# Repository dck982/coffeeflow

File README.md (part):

# coffeeflow

Modification d'une **Profitec Go** pour du *flow profiling* et du *brew by weight* : l'infusion se lance depuis un écran tactile, la pression se module, et elle s'arrête toute seule au poids cible.

## Machine d'origine

- Vanne solénoïde trois voies + pompe vibratoire 35 W + boiler
- Petit boîtier PID : consigne / mesure de température du boiler, chrono
- Vanne OPV pour limiter la pression
- Plomberie en **1/8"**
- Connexions électriques internes : cosses à languette **FASTON 6,3 × 0,8 mm** (pas de piggyback : la dérivation se fait dans un boîtier imprimé)
- Deux compartiments : **technique** (hydraulique, boiler, groupe, électricité) et **réservoir d'eau**
- Bouton **brew** en façade (Ø 16 mm) : démarrait vanne + pompe. **Supprimé** — le trou sert de passe-câble CAN vers l'écran
- LED de façade : ses cosses FASTON ont été réutilisées, la LED est réalimentée depuis le boîtier PS

## Ce que la modification ajoute

La modification pilote la pompe, la vanne et la résistance de chaudière :

1. **Pompe** — un dimmer AC 4 A en mode **DimmerLink** (I2C) fait varier la pression.
2. **Vanne solénoïde** — un SSR ouvre et ferme le circuit d'infusion.
3. **Chaudière** — le SSR Keysolu/Maxwell fourni avec la machine commande la résistance de chauffe ; sa commande 5 V passe par un HW-399 dans `boitier_pid`.

Plus de bouton brew, plus de relais NC de « mode manuel » : la commande passe par l'écran. Le système est alimenté dès que l'**interrupteur principal** de la machine est enfoncé.

Deux retours capteurs, sur le module interne :

- **Pression** sur la plomberie, en amont de la vanne (I2C 3,3 V)
- **Débit** en amont de la pompe, côté basse pression (le capteur ne tient que 3 bar)

La **température de la chaudière** vient de la sonde NTC vissée en G1/8 dans la chaudière. Son câble rejoint le boîtier de l'écran, proche de la sonde, où un ADS1115 la mesure via un pont alimenté par le **3V3 et le GND du port Sensor AD du Waveshare**. Voir [la calibration NTC/ADS1115](docs/ntc_ads1115_calibration.md).

Le **poids** vient d'une balance **Acaia Lunar** en **BLE**, lue par l'écran. La pesée du drip tray par cellule de charge est **abandonnée pour l'instant** (peser quelques grammes sur un plateau d'un kilo) — pièces et cotes conservées dans `print/parts/*_pesage*` et `docs/driptray.md`.

## Architecture électronique

**Cinq boîtiers imprimés, deux nœuds ESP32-S3.** Le 230 V ne sort pas de la machine.

```
             interrupteur principal (230 V L/N)
                          │
                    [boitier_ps]      intérieur, face ouest, le long du réservoir
                  alim RECOM 5 W · Wago            │
                          │                        └── L/N → LED de façade
              ┌───────────┴───────────┐
          5 V / GND                 L/N ×2
              │                       │
   ┌──────────┴──────────┐      [boitier_ac]   accolé à boitier_dc
   │                     │       dimmer · SSR
[boitier_dc]        [screen_*]        │    │
 XIAO ESP32-S3       Waveshare 4,3"   │    └── L/N → vanne solénoïde
 + Grove Shield      ESP32-S3         └────── L/N → pompe vibratoire
 + CAN Pal           UI · Wi-Fi · BLE
      │                   └── I2C ← ADS1115 ← NTC chaudière
      │                   │
      └──── bus CAN ──────┘   paire torsadée, par le trou Ø16 de l'ex-bouton brew
      │
      ├── I2C 3,3 V ─→ dimmer (DimmerLink)
      ├── GPIO ──────→ SSR vanne (M5Stack Unit SSR)
      ├── GPIO 3 ────→ [boitier_pid : HW-399] ─→ SSR chaudière ─→ résistance
      ├── I2C 3,3 V ←─ capteur de pression XDB401
      └── GPIO ──────← débitmètre Digmesa
```

| Nœud | Alias | Où | Rôle |
| --- | --- | --- | --- |
| **Waveshare 4,3" LCD Touch** (ESP32-S3-WROOM) | *screen*, *écran*, *waveshare* | façade, dans `screen_base` + `screen_wedge` | Interface utilisateur, algorithme d'infusion, **Wi-Fi et BLE** (Acaia Lunar) ; raccordement de la NTC chaudière via ADS1115 |
| **Seeed XIAO ESP32-S3** sur Grove Shield | *xiao*, *module interne*, *module capteurs*, *contrôleur* | intérieur, `boitier_dc`, zone froide entre le module PID et le cadran manomètre | Capteurs (XDB401, Digmesa) et actionneurs (dimmer pompe, SSR vanne, commande du SSR chaudière via HW-399) |

Les deux nœuds parlent **CAN**. L'écran est le seul à utiliser la radio.

Maquette Three.js de la machine (ouvrir dans le navigateur) : `docs/profitec_go.html`.

### Pourquoi un XIAO à l'intérieur

L'Atom Echo S3R de l'ancienne architecture est spécifié à **40 °C**. Le XIAO ESP32-S3 tient **85 °C**. Le compartiment technique monte à 45–50 °C : la marge de l'Atom est nulle, celle du XIAO est utilisable. L'écran Waveshare reste en façade, hors de cette enceinte.

---

## Boîtiers

| Boîtier | Pièces `print/parts/` | Où | Contenu |
| --- | --- | --- | --- |
| **PS** | `boitier_ps`, `couvercle_ps` | intérieur, contre la face **gauche** vue de face, le long de la séparation avec le réservoir | Alim RECOM, Wago 230 V (entrée + LED façade), Wago 5 V / GND |
| **DC** | `boitier_dc` | intérieur, **zone froide** entre le module PID et le cadran manomètre | XIAO + Grove Shield, Adafruit CAN Pal, Wago 5 V |
| **AC** | `boitier_ac` | accolé au DC | Dimmer 4 A DimmerLink, M5Stack Unit SSR |
| **PID** | `boitier_pid`, `couvercle_pid` | compartiment technique, près du contrôleur PID d'origine | HW-399, connecteurs XH et Wago de distribution 5 V / GND ; commande du SSR chaudière |
| **UI** | `screen_base`, `screen_wedge` | façade de la machine | Écran Waveshare 4,3", ADS1115 et raccordement NTC ; emplacement AMS1117 inutilisé |

Les boîtiers **AC et DC sont côte à côte et reliés par leur couvercle**, qui est commun aux deux (`couvercle_acdc`, assemblage `ensemble_boitiers`).

---

## Composants

| Rôle | Matériel retenu | Fiche |
| --- | --- | --- |
| UI / algo / radio | **Waveshare ESP32-S3-Touch-LCD-4.3** — 800 × 480, TJA1051T/3 CAN intégré, alim USB-C 5 V | `docs/datasheets/waveshare-4-3-lcd-touch.md` |
| MCU interne | **Seeed Studio XIAO ESP32-S3** sur **Grove Shield for XIAO** (8 ports Grove) | `docs/datasheets/xiao.pdf`, `docs/datasheets/grove-expansion-board.md` |
| Transceiver CAN côté XIAO | **Adafruit CAN Pal** (TJA1051T/3), [produit 5708](https://www.adafruit.com/product/5708) | — |
| Dimmer pompe | **RBDimmer AC Dimmer 4 A 1 canal**, logique 3,3 V, mode **[DimmerLink](https://www.rbdimmer.com/docs/dimmerlink-overview)** ([boutique](https://www.rbdimmer.com/shop/ac-dimmers-1/ac-dimmer-module-4a-1-channel-33v5v-logic-ac-400v-4a-6?attribute_values=48)) | — |
| SSR vanne | **M5Stack Unit SSR** (2 A), commande 3,3–5 V, zero-crossing MOC3043M | `docs/datasheets/m5stack-unit-ssr.md` |
| SSR chaudière | **Keysolu/Maxwell KS53 D-24Z20N-LQ**, fourni avec la machine ; en série entre la phase de l'interrupteur principal et la résistance, suivie de la protection thermique puis du neutre ; commande DC +/− via HW-399, FASTON mâles 4,8 mm | [Câblage](docs/cablage.md#ssr-de-chaudière-fourni-avec-la-machine) |
| Interface SSR chaudière | **HW-399 4-channel Optocoupler**, voie IN4 / OUT4, logé dans `boitier_pid` | `docs/cablage.md` |
| Température chaudière | Sonde **NTC G1/8**, pont sur le port Sensor AD et breakout **ADS1115 16 bits** sur l'I2C de l'écran | [Calibration NTC/ADS1115](docs/ntc_ads1115_calibration.md) |
| Pression | **Yufavor XDB401**, I2C, filetage **G1/8** | `docs/datasheets/xidibei_xdb401.pdf` |
| Débit | **Digmesa FHKSC 932-9525-B**, buse **1,00 mm** | `docs/datasheets/flowmeter-digmesa.pdf`, `docs/debitmetres.md` |
| Alimentation | **RECOM RAC05-05SK/277/W** — 5 W, 5 V / 1 A, encapsulée, 85–305 VAC, version fils | `docs/datasheets/RAC05-K_277.pdf` |
| Poids | **Acaia Lunar**, BLE, lue par l'écran | — |
| Câble | **Helutherm 145** — 0,75 mm² pour les ajouts 230 V, 0,25 mm² en 5 V / signaux / CAN ; puissance chaudière en 1 mm² | `docs/datasheets/helutherm145.pdf` |

Actionneurs d'origine pilotés : vanne solénoïde **OLAB 08252L50-A14-1A-G** (bobine 08000BH-J5IV, 15 VA, 220/230 V 50/60 Hz, orifice Ø 1,4 mm, joint FKM, laiton CW510L, NSF) et pompe vibratoire **OLAB Silent Green 35 W**.

---

## Le module interne (XIAO)

### Ports Grove du Shield

Le Shield expose **deux colonnes de quatre connecteurs**. XIAO en bas : colonne de **gauche = L**, colonne de **droite = R** ; le port le plus proche du XIAO est **1**, le plus éloigné **4**.

| Port | Périphérique | Bus / GPIO | Alim | Câble |
| --- | --- | --- | --- | --- |
| **R1** | Capteur de pression XDB401 | I2C — SDA **GPIO 5**, SCL **GPIO 6** | 3,3 V | Grove à clip (quelques cm) → JST SM 4 pôles, débrochable **hors du boîtier** |
| **R2** | Débitmètre Digmesa | impulsions — **GPIO 44** (D7 sur le PCB) | 5 V (voir ci-dessous) | Grove 2 fils (noir + jaune) → JST SM 3 pôles → VH3.96 côté Digmesa |
| **R3** | Adafruit CAN Pal | TWAI — TX **GPIO 7** (fil blanc), RX **GPIO 8** (fil jaune) | 3,3 V | Grove → fils dénudés dans le bornier à vis du CAN Pal |
| **R4** | M5Stack Unit SSR, **vanne** | commande — **GPIO 9** (D10, fil jaune) | 5 V, repris hors du câble | Grove 10 cm, VCC coupé à ras côté XIAO |
| **L2** | HW-399 → SSR **chaudière** | commande — **GPIO 3** (D2 sur le PCB), LOW = chauffe active | 5 V côté sortie du HW-399 | Grove → XH 2 pôles (GND, IN4) ; XH 3 pôles (GND, VCC, OUT4) côté sortie |
| **L4** | Dimmer DimmerLink | I2C — SDA **GPIO 5**, SCL **GPIO 6** | 3,3 V | Grove |

Les repères `Dn` imprimés sur le Shield ne correspondent pas toujours aux GPIO natifs du XIAO. Le [tableau de câblage](docs/cablage.md#ports-grove-du-xiao) donne les deux numérotations.

**L4 est câblé en copie de R1** pour exposer une deuxième prise I2C. Le dimmer et le capteur de pression sont donc **sur le même bus** : le dimmer n'a pas de pull-up, il profite des **4,7 kΩ du XDB401**. Conséquence : retirer le capteur de pression laisse SDA / SCL sans tirage et le dimmer ne répond plus (sauf câble très court, sur les pull-ups internes de l'ESP32). Ne pas empiler un second 4,7 kΩ côté MCU tant que le XDB401 est sur le bus.

### Pastilles du Shield

Le Shield porte une rangée de pastilles à **gauche du XIAO** (carte tenue XIAO en bas, ports vers le haut). Les trois premières sont **5 V**, **GND**, **3V3** ; la septième est **D7 / GPIO 44**.

- Un **bornier 2 poles** est soudé sur les pastilles 5 V et GND : il alimente le XIAO depuis le boîtier PS et sert de point de reprise.
- **Filtre RC du débitmètre** : résistance **1 kΩ** entre la pastille 3 (3V3) et la pastille D7 (GPIO 44), condensateur **10 nF** à cheval entre la pastille 2 (GND) et la pastille D7. Le Digmesa est un collecteur ouvert NPN : il tire la ligne à la masse mais ne la monte jamais, c'est le tirage vers 3,3 V qui fixe le niveau haut, alors même que le capteur est alimenté en 5 V. GPIO en `INPUT`, pull-up interne éteinte.

### Bus CAN

Le CAN Pal est monté au **nord de `boitier_dc`**.

- Un **bornier à vis 2,54 mm** est soudé sur ses **quatre pastilles de gauche** (VCC, GND, RX, TX de gauche à droite) et rejoint le port **R3** par un câble dénudé d'un côté, Grove de l'autre.
- Les **deux pastilles de droite** (CANH, CANL) portent un **connecteur PCB femelle JST XH 2,54 mm**.
- La ligne est une **paire torsadée Helutherm 145 0,25 mm²** : **CANL = orange, CANH = gris**. Elle chemine dans la machine et sort par le trou de l'ancien bouton brew, équipé du passe-câble imprimé (`passe_cable` + `ecrou_passe_cable`).
- À l'autre bout, un **JST SM 2 poles** la relie à un câble **JST PH 2.0 2 poles** qui se branche sur le PCB du Waveshare (transceiver TJA1051T/3 intégré, CAN sur **GPIO15 TX / GPIO16 RX**, `CAN_SEL` = EXIO5 à l'état haut).
- Les **résistances de terminaison 120 Ω sont activées par jumper des deux côtés**.

---

## Alimentation

L'alim **RECOM RAC05-05SK/277/W** vit dans `boitier_ps` et alimente **tout** : les deux modules, les capteurs et les actionneurs basse tension.

### 230 V

- **Phase et neutre** viennent de deux **cosses FASTON isolées** prises sur l'**interrupteur principal** de la machine : tant qu'il n'est pas enfoncé (clic mécanique), rien n'est sous tension.
- Les deux fils (**Helutherm 145 0,75 mm²**) entrent dans `boitier_ps` par le **sud-ouest** et vont dans les deux Wago (**phase en bas, neutre en haut**).
- De ces mêmes Wago, phase et neutre **ressortent par le sud-ouest** pour alimenter la **LED de façade** — nécessaire, ses cosses FASTON ayant été réutilisées. **Phase brun, neutre bleu.**
- Phase et neutre ressortent aussi en **arc vers le nord** pour alimenter la RECOM, juste au nord dans le même boîtier. **Phase brun, neutre bleu.**
- Deux paires 0,75 mm² sortent vers `boitier_ac`, entrant par sa **face est**, chaque paire phase-neutre maintenue par de la gaine thermo (surface de boucle nulle) : **SSR (jaune/bleu)** et **dimmer (violet/bleu)**.
- Du **SSR** repartent phase et neutre vers la **vanne solénoïde** — **phase jaune, neutre bleu**.
- Du **dimmer** repartent phase et neutre vers la **pompe** — **phase violet, neutre bleu**.

### 5 V

- **VCC 5 V et GND** sortent de la RECOM vers les **Wago 3 poles au nord de `boitier_ps`**.
- De là, deux fils **0,25 mm² rouge / noir** vont à l'**écran**, via un **bornier adaptateur USB-C**.
- Deux autres fils rouge / noir vont à `boitier_dc`, dans les deux Wago du **compartiment sud-ouest** : **3 poles à gauche = 5 V**, **2 poles à droite = GND**.
- De ces bornes partent (a) le 5 V / GND du **XIAO**, par le bornier soudé aux pastilles du Shield, et (b) le 5 V vers la **Wago 3 poles du compartiment nord-ouest**.
- La Wago nord-ouest distribue le 5 V au **SSR** (fil du câble Grove dont le VCC a été coupé à ras côté XIAO, dénudé et repris ici) et au **Digmesa** (fil rouge du câble JST SM).
- Le `boitier_pid` reçoit aussi le **5 V / GND** pour les Wago et la sortie du HW-399 qui commande le SSR chaudière. Le pont NTC du boîtier de l'écran utilise le **3V3 / GND du port Sensor AD du Waveshare**.

### Le câble du Digmesa

Côté JST SM : **3 poles, 3 fils — rouge, noir, jaune**.

- **noir + jaune** sont sertis dans un connecteur **Grove** → port **R2**
- **rouge** part seul dans la **Wago du compartiment nord-ouest** → 5 V

Côté capteur, le câble est en **VH3.96** : rouge = VCC, noir = GND, jaune = signal.

---

## Capteurs

### Température chaudière — NTC G1/8

La sonde rejoint directement le boîtier de l'écran, voisin de la chaudière. Le **3V3 du port Sensor AD du Waveshare** rejoint la Wago NTC2, la NTC et l'entrée **A0** de l'ADS1115 ; le retour NTC rejoint la Wago NTC1, **A1** et une résistance mesurée de **2,193 kΩ** vers le **GND du même port Sensor AD**. L'ADS1115 16 bits est sur le port I2C du Waveshare. A0 permet de mesurer la tension réelle d'alimentation du pont. Le LDO AMS1117 du montage initial a été retiré après la correction de la référence de masse. Schéma et paramètres de conversion : [calibration NTC/ADS1115](docs/ntc_ads1115_calibration.md).

### Pression — Yufavor XDB401

Quatre fils : **rouge VCC**, **noir GND**, **vert SDA**, **blanc SCL**. Alimenté en **3,3 V** (l'emballage annonce 5 V ; l'émulation XDB401 est complète en 3,3 V, vérifié au banc). Pull-up **4,7 kΩ** sur SDA et SCL, non débrayables — ce sont elles qui tiennent tout le bus. Filetage **G1/8**, d'où le choix (plomberie machine en 1/8").

Gaine silicone avec une **fine feuille de blindage** : **pas de continuité feuille ↔ GND**. La relier à la masse **uniquement côté ESP32** ; côté sonde, coupée et isolée, pas de boucle.

Le connecteur **JST SM** est à l'extérieur du boîtier, à proximité immédiate : la sonde se débranche sans ouvrir.

### Débit — Digmesa FHKSC 932-9525-B (buse 1,00 mm)

| | 932-9525-B (retenu) | 932-9521-A (ancien) |
| --- | --- | --- |
| Buse | **1,00 mm** | 1,20 mm |
| Sens de montage | 0° | 0° |
| Impulsions | **2382 imp/L (0,42 g)** | 1925 imp/L (0,519 g) |
| Plage linéaire | **0,033 – 0,40 L/min** | 0,075 – 0,569 L/min |
| Pré-infusion 0,5 g/s | bas de plage | sous le linéaire |
| Perte de charge | ~0,48 bar vers 0,40 L/min | ~0,42 bar à 0,6 L/min |
| **Pression max** | **3 bar à 20 °C** | 3 bar à 20 °C |

Deux conséquences qui ne relèvent pas du câblage :

- **Le capteur va en amont de la pompe**, entre le réservoir et son entrée. La machine infuse à 9 bar et la pompe monte plus haut avant l'OPV : 3 bar de tenue interdisent le circuit haute pression.
- Le **1,00 mm** met une extraction de 36 g / 28 s (0,077 L/min) à 2,3 × son minimum, et 0,5 g/s au début du linéaire. Plafond 0,40 L/min : une chasse pompe ouverte peut saturer. Comparatif complet : `docs/debitmetres.md`.

---

## Câblage

| Domaine | Fil | Connectique |
| --- | --- | --- |
| 230 V — ajouts pompe/vanne/alimentation | **Helutherm 145 0,75 mm²**, paires L/N sous gaine thermo | Wago 221 à leviers ; FASTON 6,3 × 0,8 mm côté machine |
| 230 V — puissance chaudière | **1 mm²** | SSR chaudière fourni avec la machine, FASTON mâles 4,8 mm |
| 5 V / signaux / CAN | **Helutherm 145 0,25 mm²** | Grove, JST SM (débrochable), JST XH / PH 2.0, borniers à vis 2,54 mm, Wago 221 |

Détail fil par fil, couleurs et cheminement : `docs/cablage.md`. Passage intérieur → façade : le trou **Ø 16 mm** de l'ancien bouton brew, avec le passe-câble imprimé.

## Firmware

- **`boitier_dc` (XIAO ESP32-S3)** — I2C (DimmerLink, XDB401), GPIO du SSR vanne et du SSR chaudière, comptage d'impulsions du débitmètre, TWAI/CAN.
- **UI (Waveshare ESP32-S3)** — affichage et commandes, **algorithme d'infusion** (flow control, stop on weight), Wi-Fi, BLE vers l'Acaia Lunar. L'ADS1115 sur son I2C mesure la température chaudière par une NTC.

**Langage : Rust** (`no_std`, esp-hal, embassy) sur les deux cartes, sous `firmware/rust/` ; l'interface de l'écran est en **Slint**. Le firmware C++/ESP-IDF d'origine est archivé dans `archive/firmware/`, toujours compilable : il reste la référence de comportement sur le bus CAN et en HTTP. L'outil Mac `coffeetool` (Rust) remplace les scripts Python, archivés eux aussi.

**État du firmware (2026-10-09) :** écran et module capteurs en **0.4.2**, installés et validés sur la machine, démarrage à froid compris : affichage, BLE et Wi-Fi ensemble, CAN, mise à jour de l'écran par HTTP et du module capteurs par le CAN, retour en arrière automatique. Restent à valider sur la machine : chauffe, purge et infusion. Voir [le contrat firmware](docs/firmware.md) et [la calibration NTC](docs/ntc_ads1115_calibration.md).

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
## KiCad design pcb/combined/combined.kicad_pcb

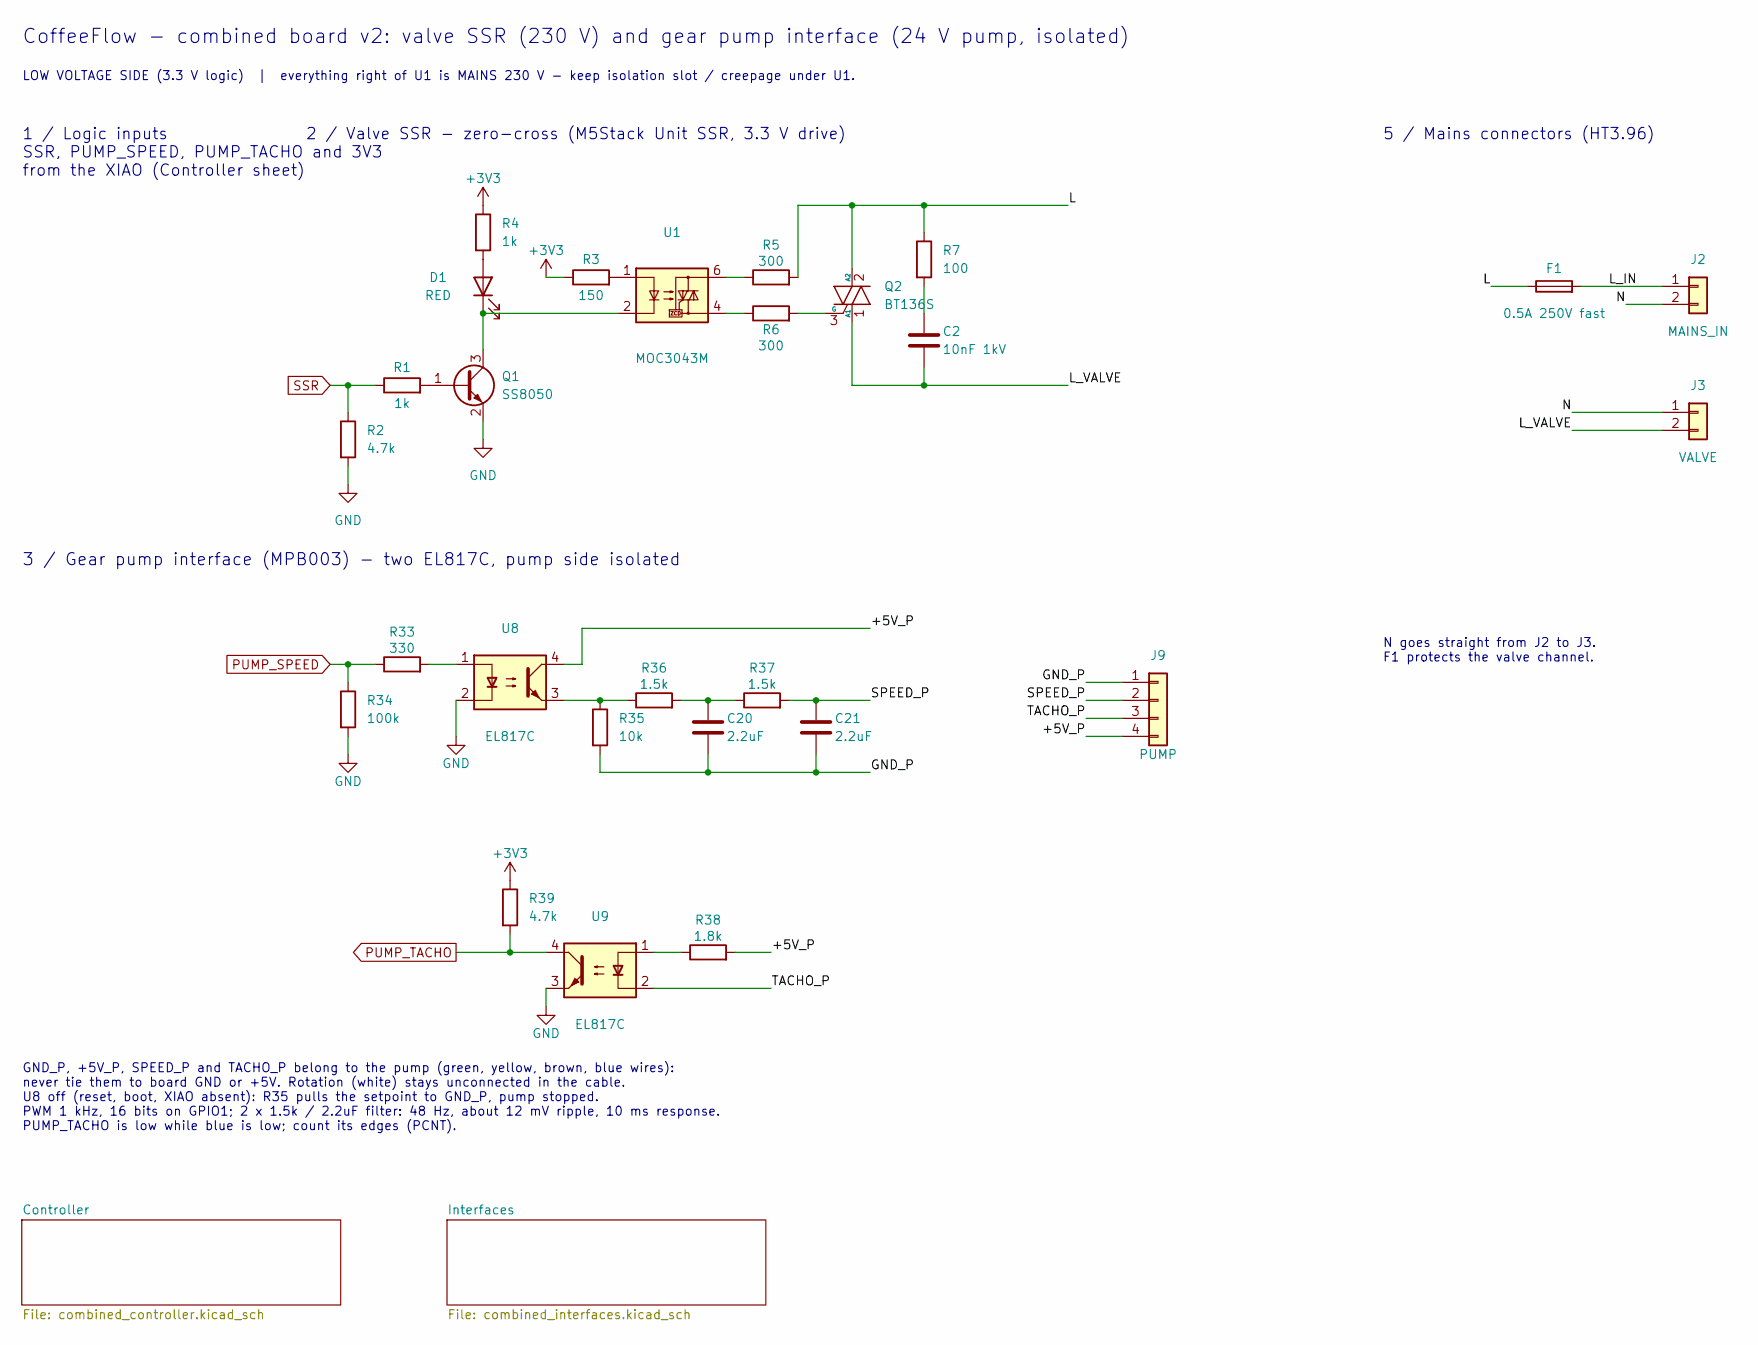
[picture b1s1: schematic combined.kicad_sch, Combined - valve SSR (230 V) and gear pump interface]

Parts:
C2: 10nF 1kV; C_1812_4532Metric; MPN FV43X103K102EFG; LCSC C394164
C20, C21: 2.2uF; C_0805_2012Metric; MPN CL21A225KBQNNNE; LCSC C377773
D1: RED; LED_0603_1608Metric; MPN KT-0603R; LCSC C2286
F1: 0.5A 250V fast; F2410; MPN MF2410F0.500TM; LCSC C91409
J2: MAINS_IN; CONN-TH_P3.96_HT396R-3.96-2P; MPN MXHT396R-3.96-02P-OE01-Cu-A; LCSC C48688287
J3: VALVE; CONN-TH_P3.96_HT396R-3.96-2P; MPN MXHT396R-3.96-02P-OE01-Cu-A; LCSC C48688287
J9: PUMP; JST_XH_B4B-XH-A_1x04_P2.50mm_Vertical; MPN B4B-XH-A(LF)(SN); LCSC C144395
Q1: SS8050; SOT-23; MPN SS8050 (Y1); LCSC C2150
Q2: BT136S; TO-252-2; MPN BT136S; LCSC C23427
R1, R4: 1k; R_0603_1608Metric; MPN 0603WAF1001T5E; LCSC C21190
R2, R39: 4.7k; R_0603_1608Metric; MPN 0603WAF4701T5E; LCSC C23162
R3: 150; R_0603_1608Metric; MPN 0603WAF1500T5E; LCSC C22808
R5, R6: 300; R_1206_3216Metric; MPN 1206W4F3000T5E; LCSC C17887
R7: 100; R_1206_3216Metric; MPN 1206W4F1000T5E; LCSC C17901
R33: 330; R_0603_1608Metric; MPN 0603WAF3300T5E; LCSC C23138
R34: 100k; R_0603_1608Metric; MPN 0603WAF1003T5E; LCSC C25803
R35: 10k; R_0603_1608Metric; MPN 0603WAF1002T5E; LCSC C25804
R36, R37: 1.5k; R_0603_1608Metric; MPN 0603WAF1501T5E; LCSC C22843
R38: 1.8k; R_0603_1608Metric; MPN 0603WAF1801T5E; LCSC C4177
U1: MOC3043M; SMDIP-6_W9.53mm_Slot; MPN MOC3043SR2M; LCSC C41809
U8, U9: EL817C; SMDIP-4_W9.53mm; MPN EL817S1(C)(TU)-F; LCSC C2912100

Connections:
+3V3: R3.1, R4.1, R39.1; also elsewhere on the board
/+5V_P: J9.4, R38.2, U8.4
/GND_P: C20.2, C21.2, J9.1, R35.2
/L: F1.1, Q2.2 (A2), R5.2, R7.1
/L_IN: F1.2, J2.1
/L_VALVE: C2.2, J3.2, Q2.1 (A1)
/N: J2.2, J3.1
/SPEED_P: C21.1, J9.2, R37.2
/TACHO_P: J9.3, U9.2
GND: Q1.2 (E), R2.2, R34.2, U8.2, U9.3; also elsewhere on the board
unnamed: C2.1, R7.2
unnamed: C20.1, R36.2, R37.1
unnamed: D1.2 (A), R4.2
unnamed: D1.1 (K), Q1.3 (C), U1.2
unnamed: Q1.1 (B), R1.2
unnamed: Q2.3 (G), R6.2
unnamed: R3.2, U1.1
unnamed: R5.1, U1.6
unnamed: R6.1, U1.4
unnamed: R33.2, U8.1
unnamed: R35.1, R36.1, U8.3
unnamed: R38.1, U9.1
PUMP_SPEED: R33.1, R34.1; also elsewhere on the board
PUMP_TACHO: R39.2, U9.4; also elsewhere on the board
SSR: R1.1, R2.1; also elsewhere on the board

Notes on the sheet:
2 / Valve SSR - zero-cross (M5Stack Unit SSR, 3.3 V drive)
5 / Mains connectors (HT3.96)
1 / Logic inputs SSR, PUMP_SPEED, PUMP_TACHO and 3V3 from the XIAO (Controller sheet)
N goes straight from J2 to J3. F1 protects the valve channel.
CoffeeFlow - combined board v2: valve SSR (230 V) and gear pump interface (24 V pump, isolated)
LOW VOLTAGE SIDE (3.3 V logic) | everything right of U1 is MAINS 230 V - keep isolation slot / creepage under U1.
3 / Gear pump interface (MPB003) - two EL817C, pump side isolated
GND_P, +5V_P, SPEED_P and TACHO_P belong to the pump (green, yellow, brown, blue wires): never tie them to board GND or +5V. Rotation (white) stays unconnected in the cable. U8 off (reset, boot, XIAO absent): R35 pulls the setpoint to GND_P, pump stopped. PWM 1 kHz, 16 bits on GPIO1; 2 x 1.5k / 2.2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

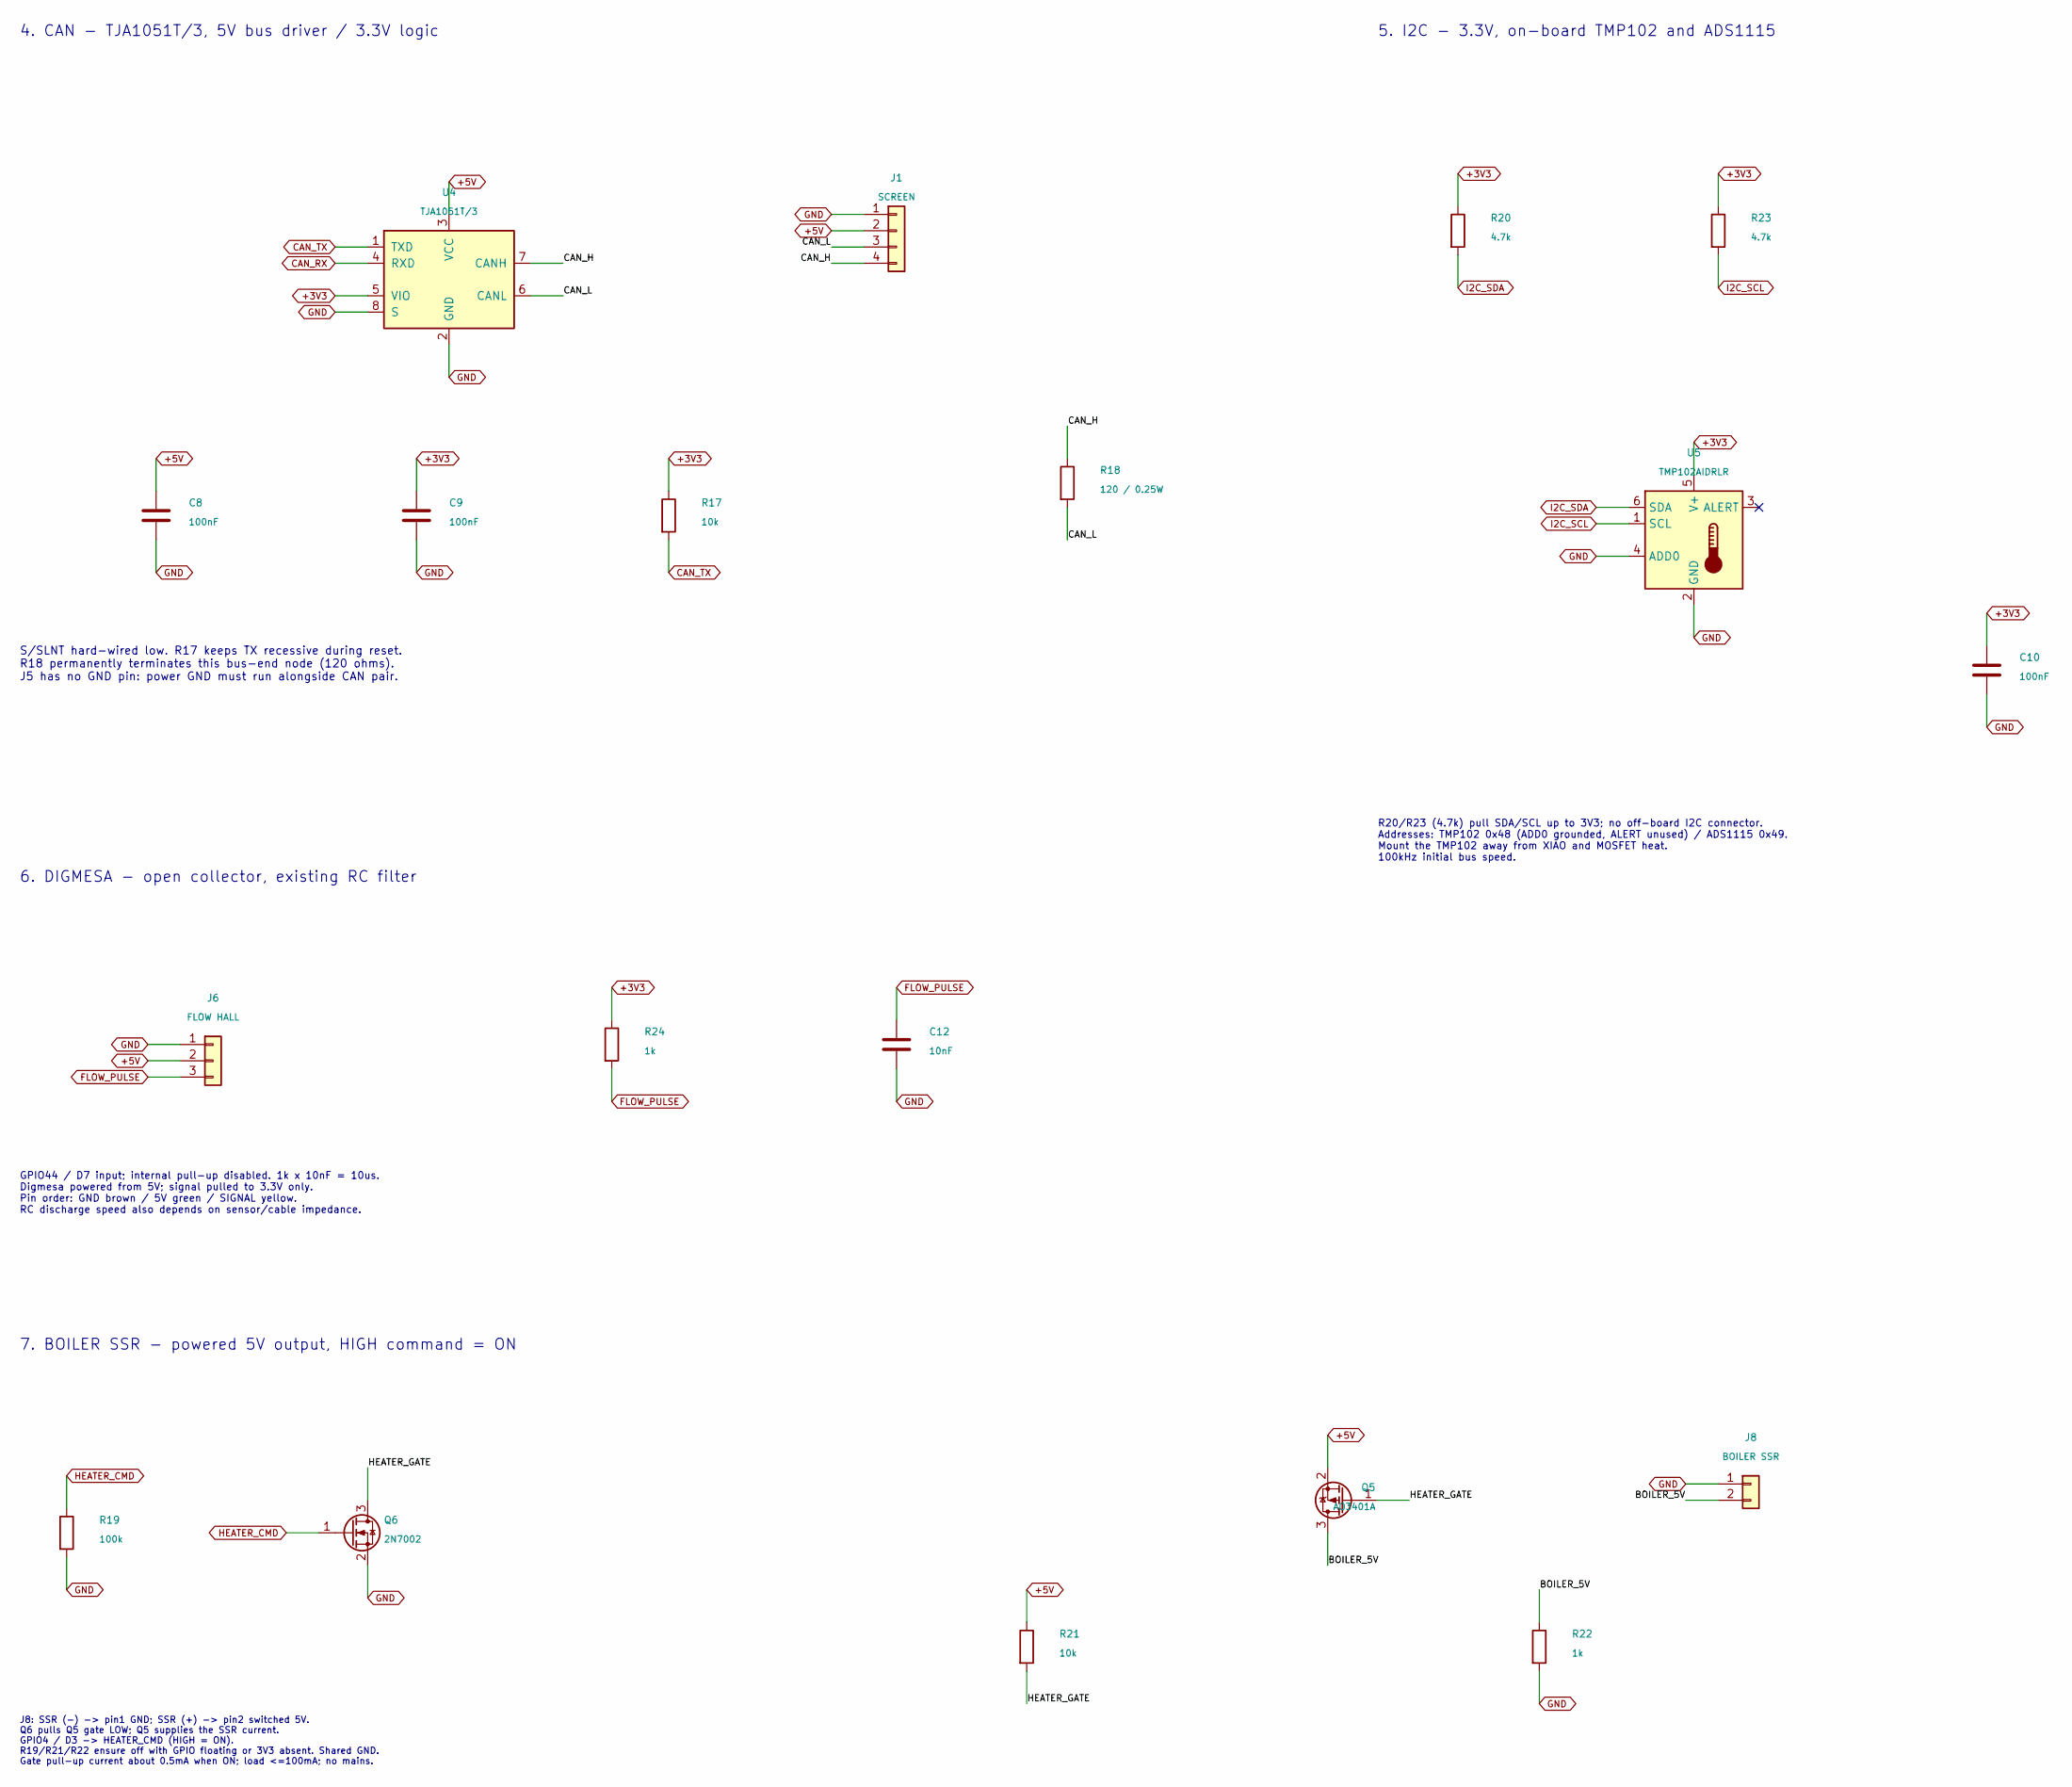
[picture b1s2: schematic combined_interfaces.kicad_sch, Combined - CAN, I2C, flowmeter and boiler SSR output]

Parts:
C8, C9, C10: 100nF; C_0603_1608Metric; MPN CC0603KRX7R9BB104; LCSC C14663
C12: 10nF; C_0603_1608Metric; MPN 0603B103K500NT; LCSC C57112
J1: SCREEN; JST_XH_B4B-XH-A_1x04_P2.50mm_Vertical; MPN B4B-XH-A(LF)(SN); LCSC C144395
J6: FLOW HALL; CONN-TH_P3.96_HT396V-3.96-3P; MPN HT396V-3.96-3P; LCSC C577789
J8: BOILER SSR; CONN-TH_P3.96_HT396V-3.96-2P; MPN HT396V-3.96-2P; LCSC C577788
Q5: AO3401A; SOT-23; MPN AO3401A; LCSC C15127
Q6: 2N7002; SOT-23; MPN 2N7002; LCSC C8545
R17, R21: 10k; R_0603_1608Metric; MPN 0603WAF1002T5E; LCSC C25804
R18: 120 / 0.25W; R_1206_3216Metric; MPN 1206W4F1200T5E; LCSC C17909
R19: 100k; R_0603_1608Metric; MPN 0603WAF1003T5E; LCSC C25803
R20, R23: 4.7k; R_0603_1608Metric; MPN 0603WAF4701T5E; LCSC C23162
R22, R24: 1k; R_0603_1608Metric; MPN 0603WAF1001T5E; LCSC C21190
U4: TJA1051T/3; SOIC-8_3.9x4.9mm_P1.27mm; MPN TJA1051T/3/1J; LCSC C38695
U5: TMP102AIDRLR; SOT-563; MPN TMP102AIDRLR; LCSC C99269

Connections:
+3V3: C9.1, C10.1, R17.1, R20.1, R23.1, R24.1, U4.5 (VIO), U5.5 (V+); also elsewhere on the board
+5V: C8.1, J1.2, J6.2, Q5.2 (S), R21.1, U4.3 (VCC); also elsewhere on the board
/Interfaces/BOILER_5V: J8.2, Q5.3 (D), R22.1
/Interfaces/CAN_H: J1.4, R18.1, U4.7 (CANH)
/Interfaces/CAN_L: J1.3, R18.2, U4.6 (CANL)
/Interfaces/HEATER_GATE: Q5.1 (G), Q6.3 (D), R21.2
CAN_RX: U4.4 (RXD); also elsewhere on the board
CAN_TX: R17.2, U4.1 (TXD); also elsewhere on the board
FLOW_PULSE: C12.1, J6.3, R24.2; also elsewhere on the board
GND: C8.2, C9.2, C10.2, C12.2, J1.1, J6.1, J8.1, Q6.2 (S), R19.2, R22.2, U4.2 (GND), U4.8 (S), U5.2 (GND), U5.4 (ADD0); also elsewhere on the board
HEATER_CMD: Q6.1 (G), R19.1; also elsewhere on the board
I2C_SCL: R23.2, U5.1 (SCL); also elsewhere on the board
I2C_SDA: R20.2, U5.6 (SDA); also elsewhere on the board

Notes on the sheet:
7. BOILER SSR - powered 5V output, HIGH command = ON
5. I2C - 3.3V, on-board TMP102 and ADS1115
4. CAN - TJA1051T/3, 5V bus driver / 3.3V logic
6. DIGMESA - open collector, existing RC filter
R20/R23 (4.7k) pull SDA/SCL up to 3V3; no off-board I2C connector. Addresses: TMP102 0x48 (ADD0 grounded, ALERT unused) / ADS1115 0x49. Mount the TMP102 away from XIAO and MOSFET heat. 100kHz initial bus speed.
S/SLNT hard-wired low. R17 keeps TX recessive during reset. R18 permanently terminates this bus-end node (120 ohms). J5 has no GND pin: power GND must run alongside CAN pair.
J8: SSR (-) -> pin1 GND; SSR (+) -> pin2 switched 5V. Q6 pulls Q5 gate LOW; Q5 supplies the SSR current. GPIO4 / D3 -> HEATER_CMD (HIGH = ON). R19/R21/R22 ensure off with GPIO floating or 3V3 absent. Shared GND. Gate pull-up current about 0.5mA when ON; load <=100mA; no mains.
GPIO44 / D7 input; internal pull-up disabled. 1k x 10nF = 10us. Digmesa powered from 5V; signal pulled to 3.3V only. Pin order: GND brown / 5V green / SIGNAL yellow. RC discharge speed also depends on sensor/cable impedance.

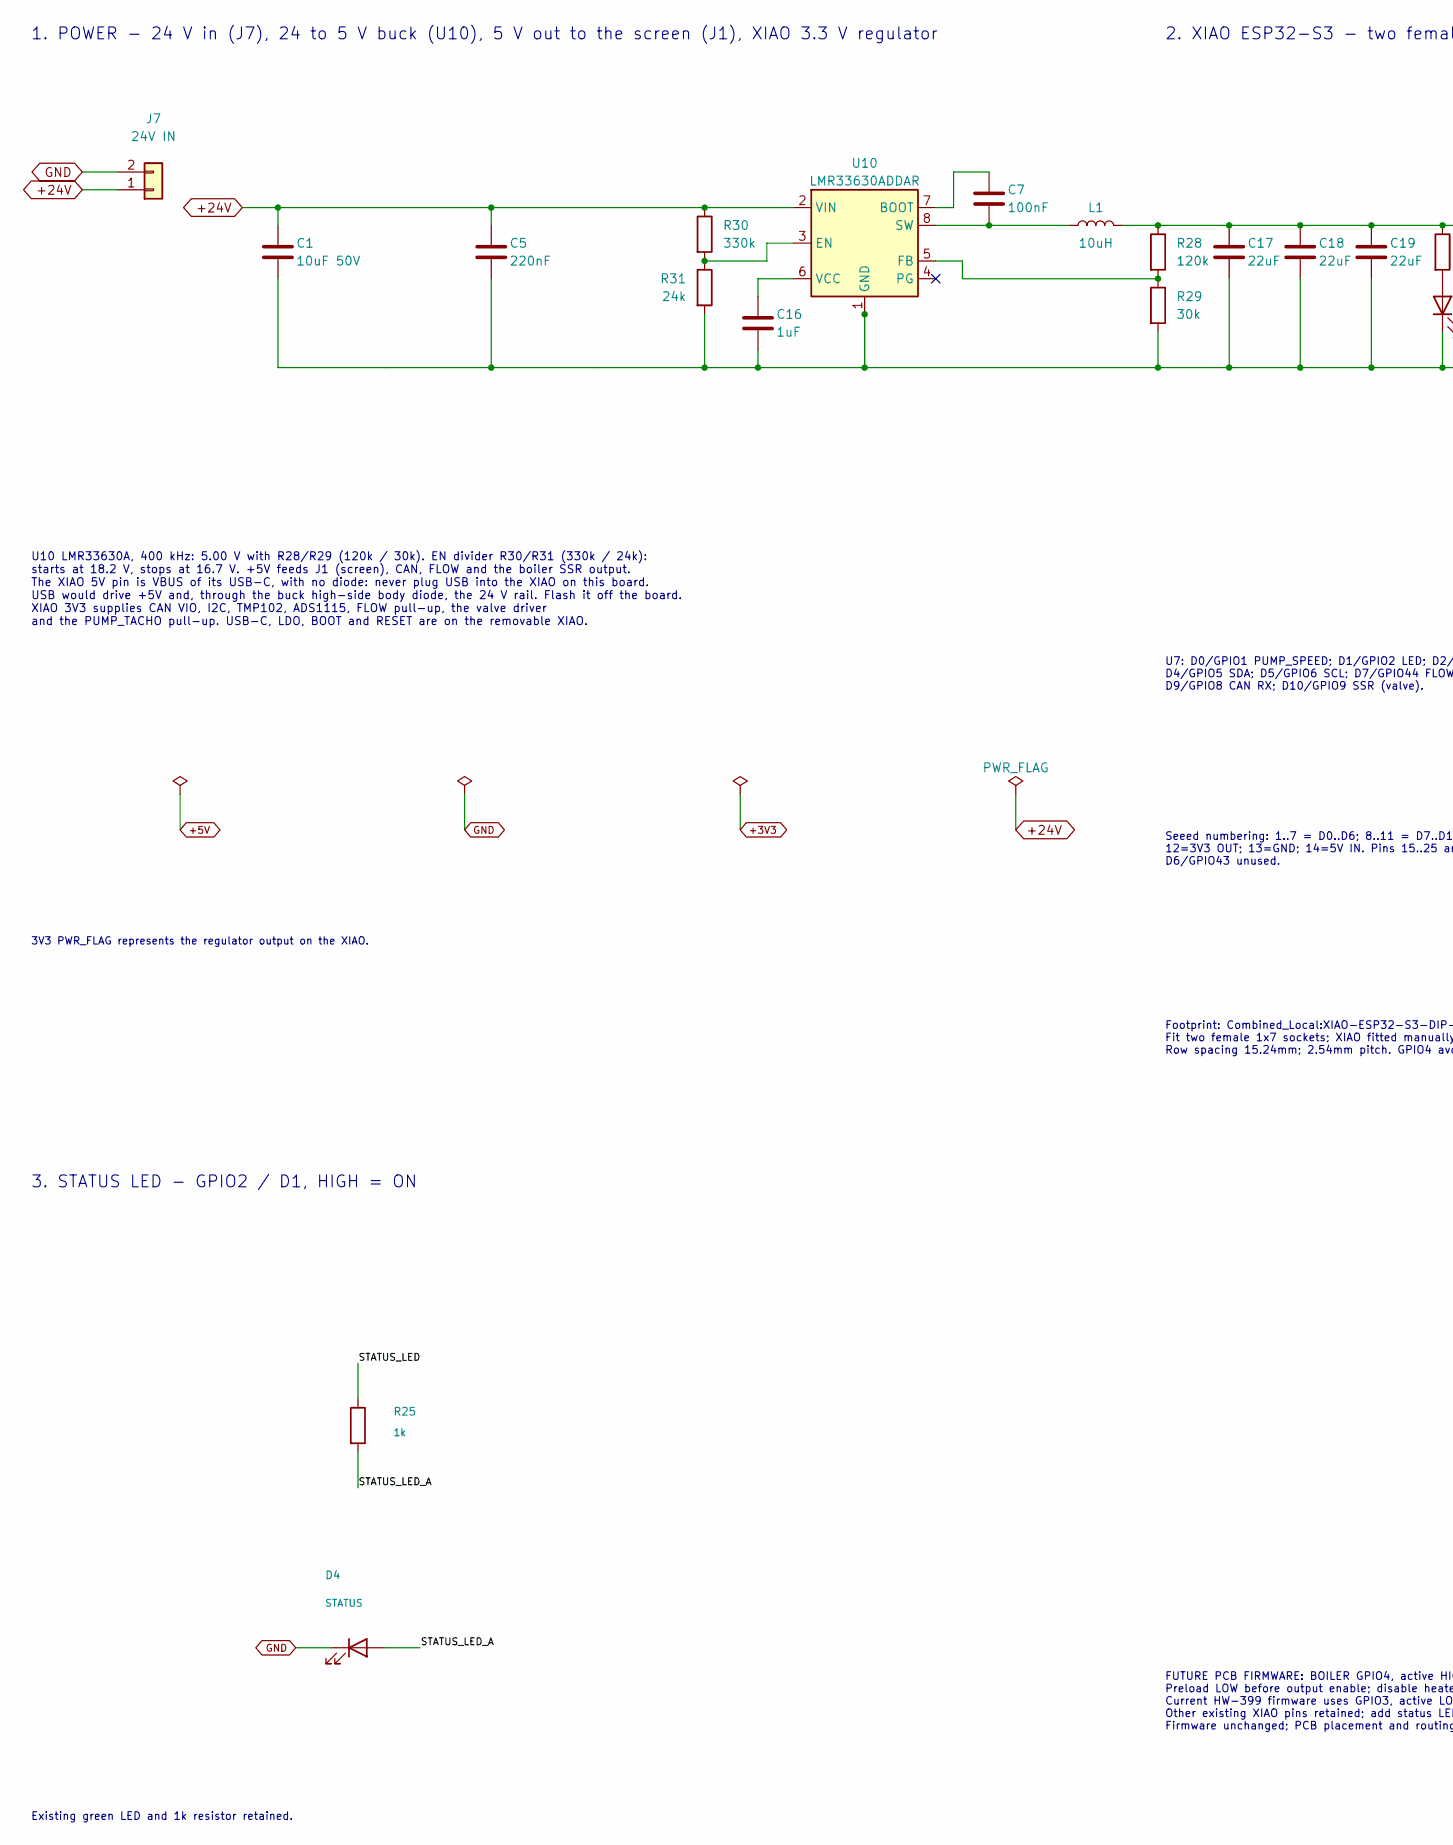
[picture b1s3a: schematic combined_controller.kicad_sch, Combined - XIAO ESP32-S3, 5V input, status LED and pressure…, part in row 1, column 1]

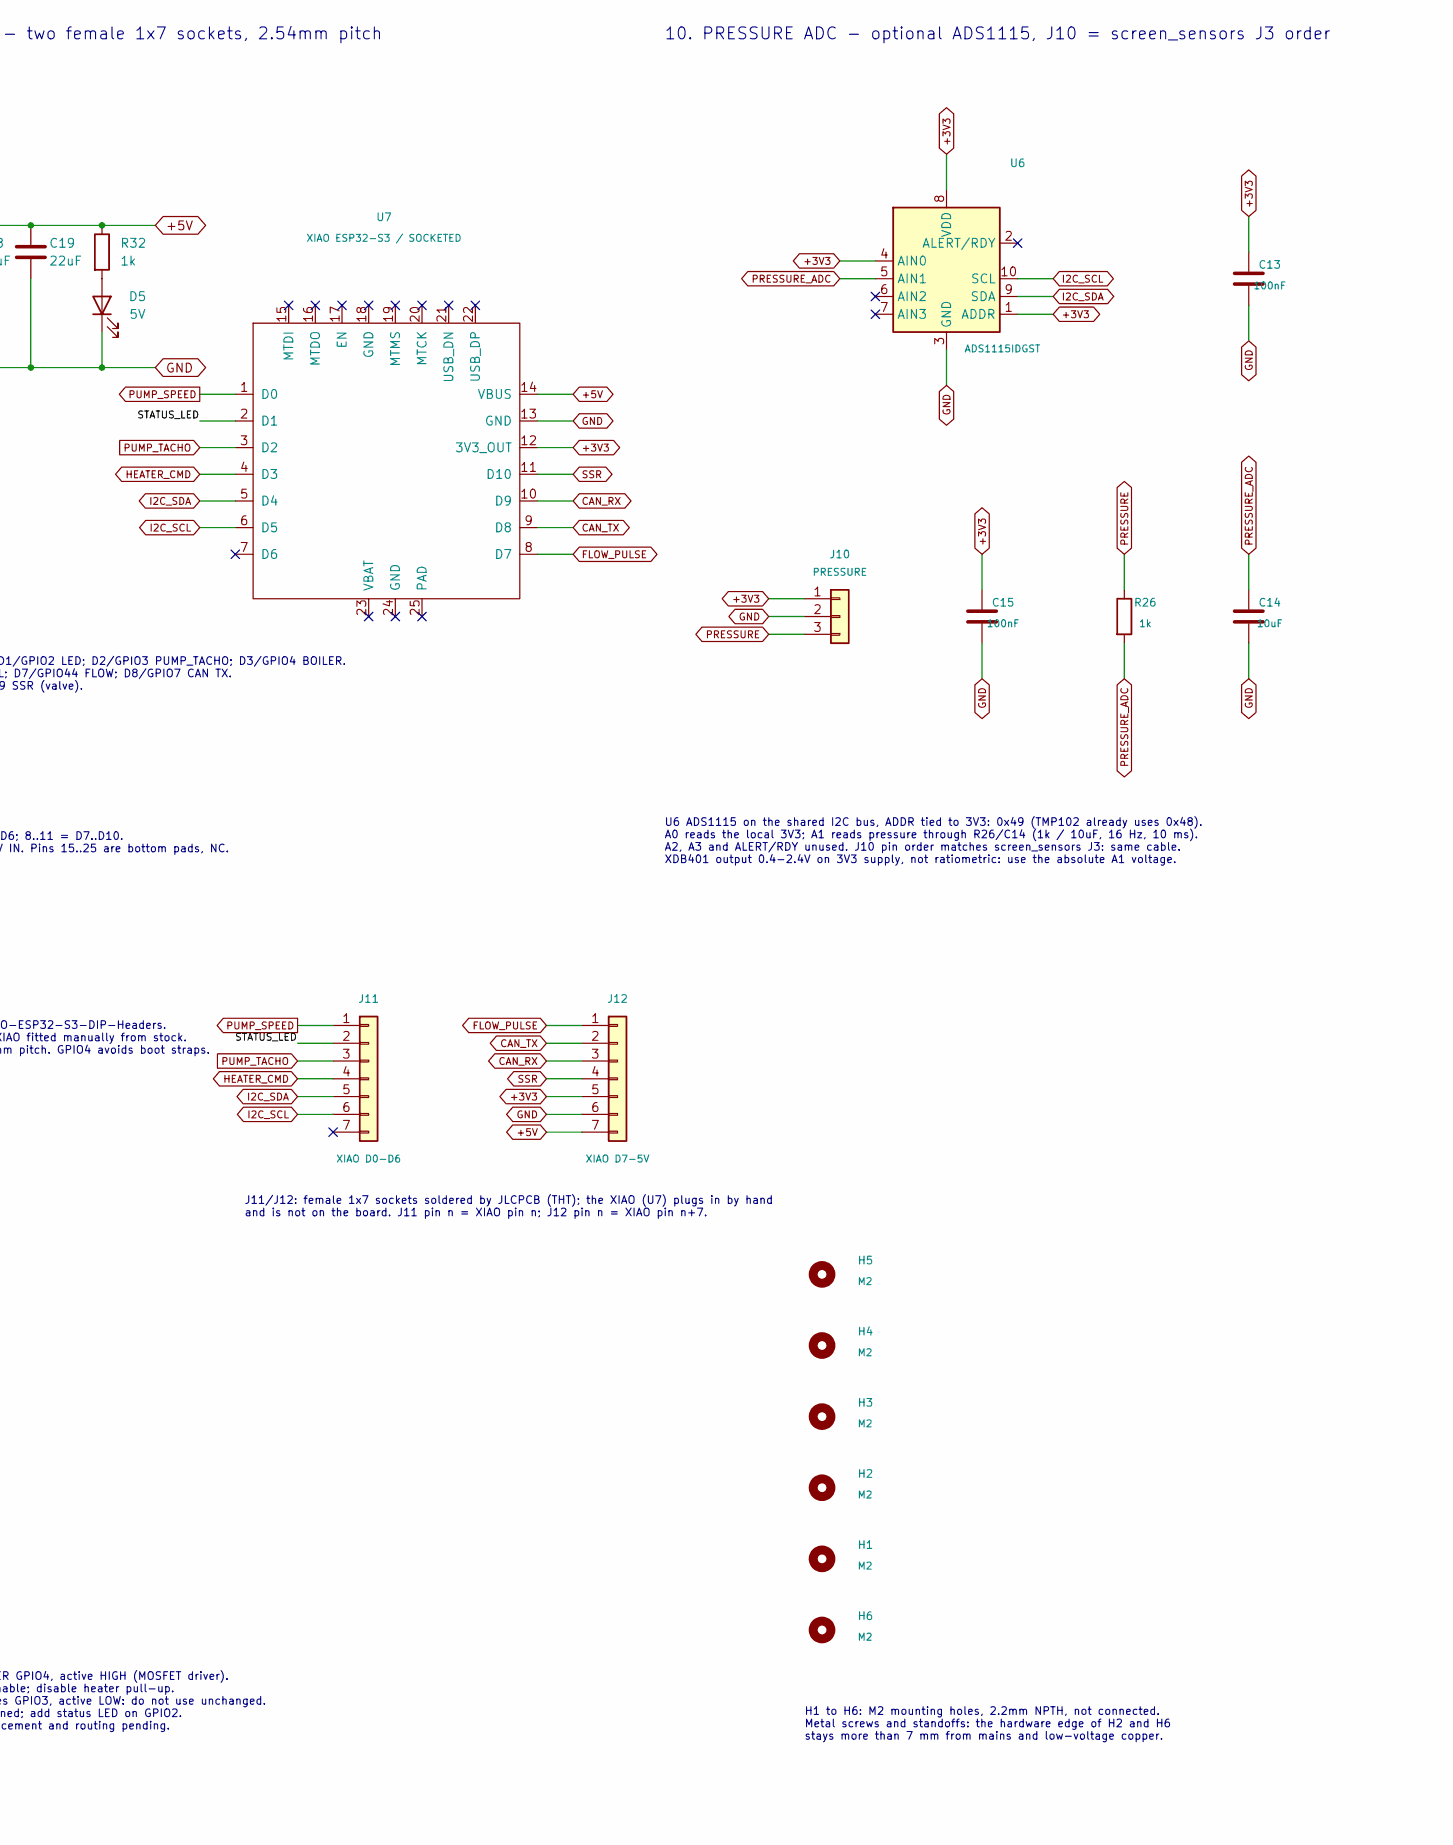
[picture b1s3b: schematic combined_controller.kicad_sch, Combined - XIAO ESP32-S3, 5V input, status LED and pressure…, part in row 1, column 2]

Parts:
C1: 10uF 50V; C_1206_3216Metric; MPN CL31A106KBHNNNE; LCSC C13585
C5: 220nF; C_0805_2012Metric; MPN CL21B224KBFNNNE; LCSC C5378
C7, C13, C15: 100nF; C_0603_1608Metric; MPN CC0603KRX7R9BB104; LCSC C14663
C14: 10uF; C_0603_1608Metric; MPN CL10A106KP8NNNC; LCSC C19702
C16: 1uF; C_0603_1608Metric; MPN CL10A105KB8NNNC; LCSC C15849
C17, C18, C19: 22uF; C_1206_3216Metric; MPN CL31A226KAHNNNE; LCSC C12891
D4: STATUS; LED_0603_1608Metric; MPN KT-0603R; LCSC C2286
D5: 5V; LED_0603_1608Metric; MPN KT-0603R; LCSC C2286
H1, H2, H3, H4, H5, H6: M2; MountingHole_2.2mm_M2; MPN M2 / 2.2mm
J7: 24V IN; CONN-TH_P3.96_HT396V-3.96-2P; MPN HT396V-3.96-2P; LCSC C577788
J10: PRESSURE; JST_XH_B3B-XH-A_1x03_P2.50mm_Vertical; MPN B3B-XH-A(LF)(SN); LCSC C144394
J11: XIAO D0-D6; XIAO_Socket_1x07_P2.54mm_Vertical; MPN HC-PM254-5.0H-1x7PZ; LCSC C27985232
J12: XIAO D7-5V; XIAO_Socket_1x07_P2.54mm_Vertical; MPN HC-PM254-5.0H-1x7PZ; LCSC C27985232
L1: 10uH; L_Changjiang_FXL0630; MPN FXL0630-100-M; LCSC C167223
R25, R26, R32: 1k; R_0603_1608Metric; MPN 0603WAF1001T5E; LCSC C21190
R28: 120k; R_0603_1608Metric; MPN 0603WAF1203T5E; LCSC C25808
R29: 30k; R_0603_1608Metric; MPN 0603WAF3002T5E; LCSC C22984
R30: 330k; R_0603_1608Metric; MPN 0603WAF3303T5E; LCSC C23137
R31: 24k; R_0603_1608Metric; MPN 0603WAF2402T5E; LCSC C23352
U6: ADS1115IDGST; TSSOP-10_3x3mm_P0.5mm; MPN ADS1115IDGST; LCSC C468683
U7: XIAO ESP32-S3 / SOCKETED; XIAO-ESP32-S3-DIP-Headers; MPN Seeed Studio XIAO ESP32-S3
U10: LMR33630ADDAR; Texas_HSOP-8-1EP_3.9x4.9mm_P1.27mm_ThermalVias; MPN LMR33630ADDAR; LCSC C841384

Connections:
+3V3: C13.1, C15.1, J10.1, J12.5, U6.1 (ADDR), U6.4 (AIN0), U6.8 (VDD), U7.12 (3V3_OUT); also elsewhere on the board
+5V: C17.1, C18.1, C19.1, J12.7, L1.2, R28.1, R32.1, U7.14 (VBUS); also elsewhere on the board
+24V: C1.1, C5.1, J7.1, R30.1, U10.2 (VIN)
/Controller/STATUS_LED: J11.2, R25.1, U7.2 (D1)
/Controller/STATUS_LED_A: D4.2 (A), R25.2
CAN_RX: J12.3, U7.10 (D9); also elsewhere on the board
CAN_TX: J12.2, U7.9 (D8); also elsewhere on the board
FLOW_PULSE: J12.1, U7.8 (D7); also elsewhere on the board
GND: C1.2, C5.2, C13.2, C14.2, C15.2, C16.2, C17.2, C18.2, C19.2, D4.1 (K), D5.1 (K), J7.2, J10.2, J12.6, R29.2, R31.2, U6.3 (GND), U7.13 (GND), U10.1 (GND), U10.9 (GND); also elsewhere on the board
HEATER_CMD: J11.4, U7.4 (D3); also elsewhere on the board
I2C_SCL: J11.6, U6.10 (SCL), U7.6 (D5); also elsewhere on the board
I2C_SDA: J11.5, U6.9 (SDA), U7.5 (D4); also elsewhere on the board
unnamed: D5.2 (A), R32.2
unnamed: C7.1, U10.7 (BOOT)
unnamed: R30.2, R31.1, U10.3 (EN)
unnamed: R28.2, R29.1, U10.5 (FB)
unnamed: C7.2, L1.1, U10.8 (SW)
unnamed: C16.1, U10.6 (VCC)
PRESSURE: J10.3, R26.1
PRESSURE_ADC: C14.1, R26.2, U6.5 (AIN1)
PUMP_SPEED: J11.1, U7.1 (D0); also elsewhere on the board
PUMP_TACHO: J11.3, U7.3 (D2); also elsewhere on the board
SSR: J12.4, U7.11 (D10); also elsewhere on the board

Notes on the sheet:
Footprint: Combined_Local:XIAO-ESP32-S3-DIP-Headers. Fit two female 1x7 sockets; XIAO fitted manually from stock. Row spacing 15.24mm; 2.54mm pitch. GPIO4 avoids boot straps.
Existing green LED and 1k resistor retained.
U7: D0/GPIO1 PUMP_SPEED; D1/GPIO2 LED; D2/GPIO3 PUMP_TACHO; D3/GPIO4 BOILER. D4/GPIO5 SDA; D5/GPIO6 SCL; D7/GPIO44 FLOW; D8/GPIO7 CAN TX. D9/GPIO8 CAN RX; D10/GPIO9 SSR (valve).
1. POWER - 24 V in (J7), 24 to 5 V buck (U10), 5 V out to the screen (J1), XIAO 3.3 V regulator
3. STATUS LED - GPIO2 / D1, HIGH = ON
3V3 PWR_FLAG represents the regulator output on the XIAO.
10. PRESSURE ADC - optional ADS1115, J10 = screen_sensors J3 order
U10 LMR33630A, 400 kHz: 5.00 V with R28/R29 (120k / 30k). EN divider R30/R31 (330k / 24k): starts at 18.2 V, stops at 16.7 V. +5V feeds J1 (screen), CAN, FLOW and the boiler SSR output. The XIAO 5V pin is VBUS of its USB-C, with no diode: never plug USB into the XIAO on this board. USB would drive 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
FUTURE PCB FIRMWARE: BOILER GPIO4, active HIGH (MOSFET driver). Preload LOW before output enable; disable heater pull-up. Current HW-399 firmware uses GPIO3, active LOW: do not use unchanged. Other existing XIAO pins retained; add status LED on GPIO2. Firmware unchanged; PCB placement and routing p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
J11/J12: female 1x7 sockets soldered by JLCPCB (THT); the XIAO (U7) plugs in by hand and is not on the board. J11 pin n = XIAO pin n; J12 pin n = XIAO pin n+7.
Seeed numbering: 1..7 = D0..D6; 8..11 = D7..D10. 12=3V3 OUT; 13=GND; 14=5V IN. Pins 15..25 are bottom pads, NC. D6/GPIO43 unused.
U6 ADS1115 on the shared I2C bus, ADDR tied to 3V3: 0x49 (TMP102 already uses 0x48). A0 reads the local 3V3; A1 reads pressure through R26/C14 (1k / 10uF, 16 Hz, 10 ms). A2, A3 and ALERT/RDY unused. J10 pin order matches screen_sensors J3: same cable. XDB401 output 0.4-2.4V on 3V3 supply, not ratio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
H1 to H6: M2 mounting holes, 2.2mm NPTH, not connected. Metal screws and standoffs: the hardware edge of H2 and H6 stays more than 7 mm from mains and low-voltage copper.
2. XIAO ESP32-S3 - two female 1x7 sockets, 2.54mm pitch
